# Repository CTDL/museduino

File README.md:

# museduino
an open source electronics environment for exhibits

Docs: <a href="https://museduino.org">museduino.org</a>

## PCB design files and Schematics

All files are under <a href="https://github.com/CTDL/museduino/tree/master/hardware">hardware</a>  folder and subdivided by PCB design software.

ExpressPCB folder contains versions 2.2 and below. Kicad folder is organized by board name contains its own versions (3.0 or greater).

View changelog.md for further information on changes between versions.

## Tutorials and Circuit Diagrams
Content for workshops and Museduino guides can be found under 
<a href="https://github.com/CTDL/museduino/tree/master/tutorials">tutorials</a> folder.

## Solder Instructions
Component guides and step-by-step instructions coming soon.
<a href="https://github.com/CTDL/museduino/tree/master/solder-instructions">solder-instructions</a> folder.

## Open Source
Museduino 4.0 is certified as OSHWA-compliant open source hardware.

<a href="https://certification.oshwa.org/us002128.html">certification.oshwa.org/us002128.html</a>

## License

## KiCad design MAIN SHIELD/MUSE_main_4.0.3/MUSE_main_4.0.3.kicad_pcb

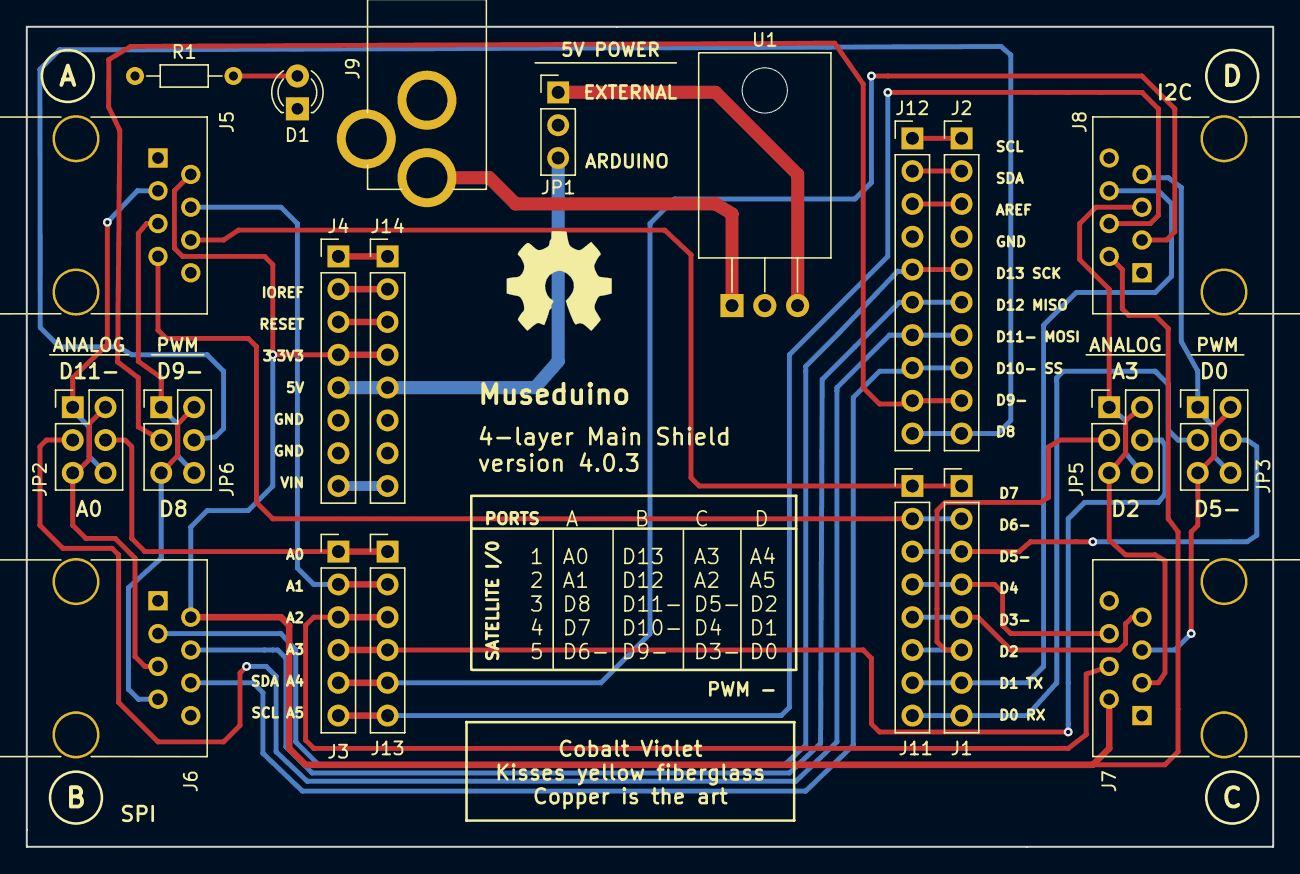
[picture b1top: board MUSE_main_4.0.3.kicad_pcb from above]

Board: 4 copper layers, 96.5 x 63.5 mm, 21 parts (0 on the bottom side), 42 nets.

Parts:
D1: LED; LED_D3.0mm
J1, J4, J11, J14: CONN_01X08; Pin_Header_Straight_1x08_Pitch2.54mm
J2, J12: CONN_01X10; Pin_Header_Straight_1x10_Pitch2.54mm
J3, J13: CONN_01X06; Pin_Header_Straight_1x06_Pitch2.54mm
J5, J6, J7, J8: CONN_01X08; RJ45_8
J9: BARREL_JACK; BARREL_JACK_RND
JP1: CONN_01X03; Pin_Header_Straight_1x03_Pitch2.54mm
JP2, JP3, JP5, JP6: CONN_02X03; Pin_Header_Straight_2x03_Pitch2.54mm
R1: 470; R_Axial_DIN0204_L3.6mm_D1.6mm_P7.62mm_Horizontal
U1: LM7805CT; TO-220_Horizontal

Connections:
+3V3: J4.4, J5.2, J6.2, J7.2, J8.2, J14.4
+5V: J5.1, J6.1, J7.1, J8.1, JP1.2, R1.1
+5V-ARD: J4.5, J14.5, JP1.3
+5V_REG: JP1.1, U1.3
A0: J3.1, J13.1, JP2.4
A1: J3.2, J5.4, J13.2
A2: J3.3, J7.4, J13.3
A3: J3.4, J13.4, JP5.4
A4_SDA: J3.5, J8.3, J13.5
A5_SCL: J3.6, J8.4, J13.6
AREF: J2.3, J12.3
D0: J1.8, J11.8, JP3.3
D1: J1.7, J8.6, J11.7
D2: J1.6, J11.6, JP5.3
D3: J1.5, J7.7, J11.5
D4: J1.4, J7.6, J11.4
D5: J1.3, J11.3, JP3.4
D6: J1.2, J5.7, J11.2
D7: J1.1, J5.6, J11.1
D8: J2.10, J12.10, JP6.4
D9: J2.9, J12.9, JP6.3
D10: J2.8, J6.6, J12.8
D11: J2.7, J12.7, JP2.3
D12: J2.6, J6.4, J12.6
D13: J2.5, J6.3, J12.5
GND: D1.1, J2.4, J4.6, J4.7, J5.8, J6.8, J7.8, J8.8, J9.2, J12.4, J14.6, J14.7, U1.2
IO-REF: J4.2, J14.2
J2-1: J2.1, J12.1
J2-2: J2.2, J12.2
J4-1: J4.1, J14.1
J5-3: J5.3, JP2.1, JP2.6
J5-5: J5.5, JP6.1, JP6.6
J6-5: J6.5, JP2.2, JP2.5
J6-7: J6.7, JP6.2, JP6.5
J7-3: J7.3, JP5.2, JP5.5
J7-5: J7.5, JP3.2, JP3.5
J8-5: J8.5, JP5.1, JP5.6
J8-7: J8.7, JP3.1, JP3.6
unnamed: D1.2, R1.2
unnamed: J9.1, U1.1
RST: J4.3, J14.3
Vin: J4.8, J14.8

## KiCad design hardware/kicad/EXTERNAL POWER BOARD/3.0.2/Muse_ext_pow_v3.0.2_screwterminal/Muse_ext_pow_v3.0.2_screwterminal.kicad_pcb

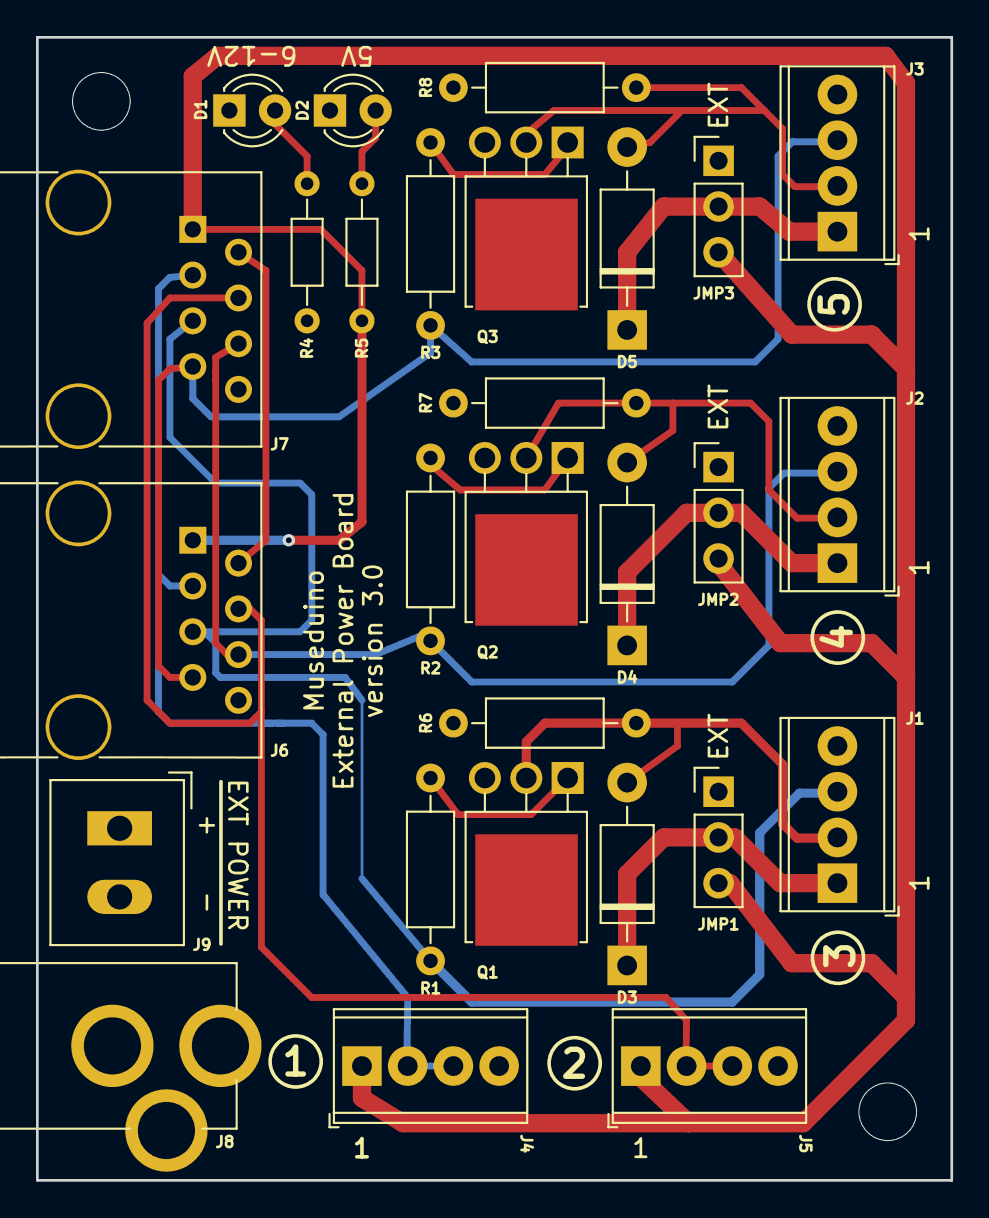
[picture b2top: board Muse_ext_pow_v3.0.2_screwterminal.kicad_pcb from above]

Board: 4 copper layers, 50.8 x 63.5 mm, 30 parts (0 on the bottom side), 20 nets.

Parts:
D1, D2: LED; LED_D3.0mm
D3, D4, D5: 1N4001; D_DO-41_SOD81_P10.16mm_Horizontal
J1, J2, J3, J4, J5: CONN_01X04; TerminalBlock_Phoenix_MPT-0,5-4-2.54_1x04_P2.54mm_Horizontal
J6, J7: RJ45_01X08; RJ45_8
J8: Barrel_Jack; BARREL_JACK_RND
J9: Conn_01x02; FCI_3.81-mm_screw_terminal
JMP1, JMP2, JMP3: Conn_01x03_Male; Pin_Header_Straight_1x03_Pitch2.54mm
Mount_Hole: MountingHole_3.2mm_M3
Mount_hole: MountingHole_3.2mm_M3
Q1, Q2, Q3: NTD3055L104-1G; TO-251-1EP_IPAK_Horizontal_smorg
R1, R2, R3: 220; R_Axial_DIN0207_L6.3mm_D2.5mm_P10.16mm_Horizontal
R4, R5: 470; R_Axial_DIN0204_L3.6mm_D1.6mm_P7.62mm_Horizontal
R6, R7, R8: 10k; R_Axial_DIN0207_L6.3mm_D2.5mm_P10.16mm_Horizontal

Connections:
+3V3: J6.2, J7.2
+5V: J4.1, J5.1, J6.1, J7.1, JMP1.3, JMP2.3, JMP3.3, R5.1
GND: D1.1, D2.1, J1.4, J2.4, J3.4, J4.4, J5.4, J6.8, J7.8, J8.2, J9.2, Q1.3, Q2.3, Q3.3, R6.2, R7.2, R8.2
unnamed: D1.2, R4.2
unnamed: D2.2, R5.2
unnamed: D3.2, J1.2, Q1.2, R6.1
unnamed: D4.2, J2.2, Q2.2, R7.1
unnamed: D5.2, J3.2, Q3.2, R8.1
unnamed: Q1.1, R1.1
unnamed: Q2.1, R2.1
unnamed: Q3.1, R3.1
Sense_1: J4.2, J4.3, J6.3, J7.3
Sense_2: J5.2, J5.3, J6.4, J7.4
Sense_3: J1.3, J6.5, J7.5, R1.2
Sense_4: J2.3, J6.6, J7.6, R2.2
Sense_5: J3.3, J6.7, J7.7, R3.2
Ve3: D3.1, J1.1, JMP1.2
Ve4: D4.1, J2.1, JMP2.2
Ve5: D5.1, J3.1, JMP3.2
Vext: J8.1, J9.1, JMP1.1, JMP2.1, JMP3.1, R4.1

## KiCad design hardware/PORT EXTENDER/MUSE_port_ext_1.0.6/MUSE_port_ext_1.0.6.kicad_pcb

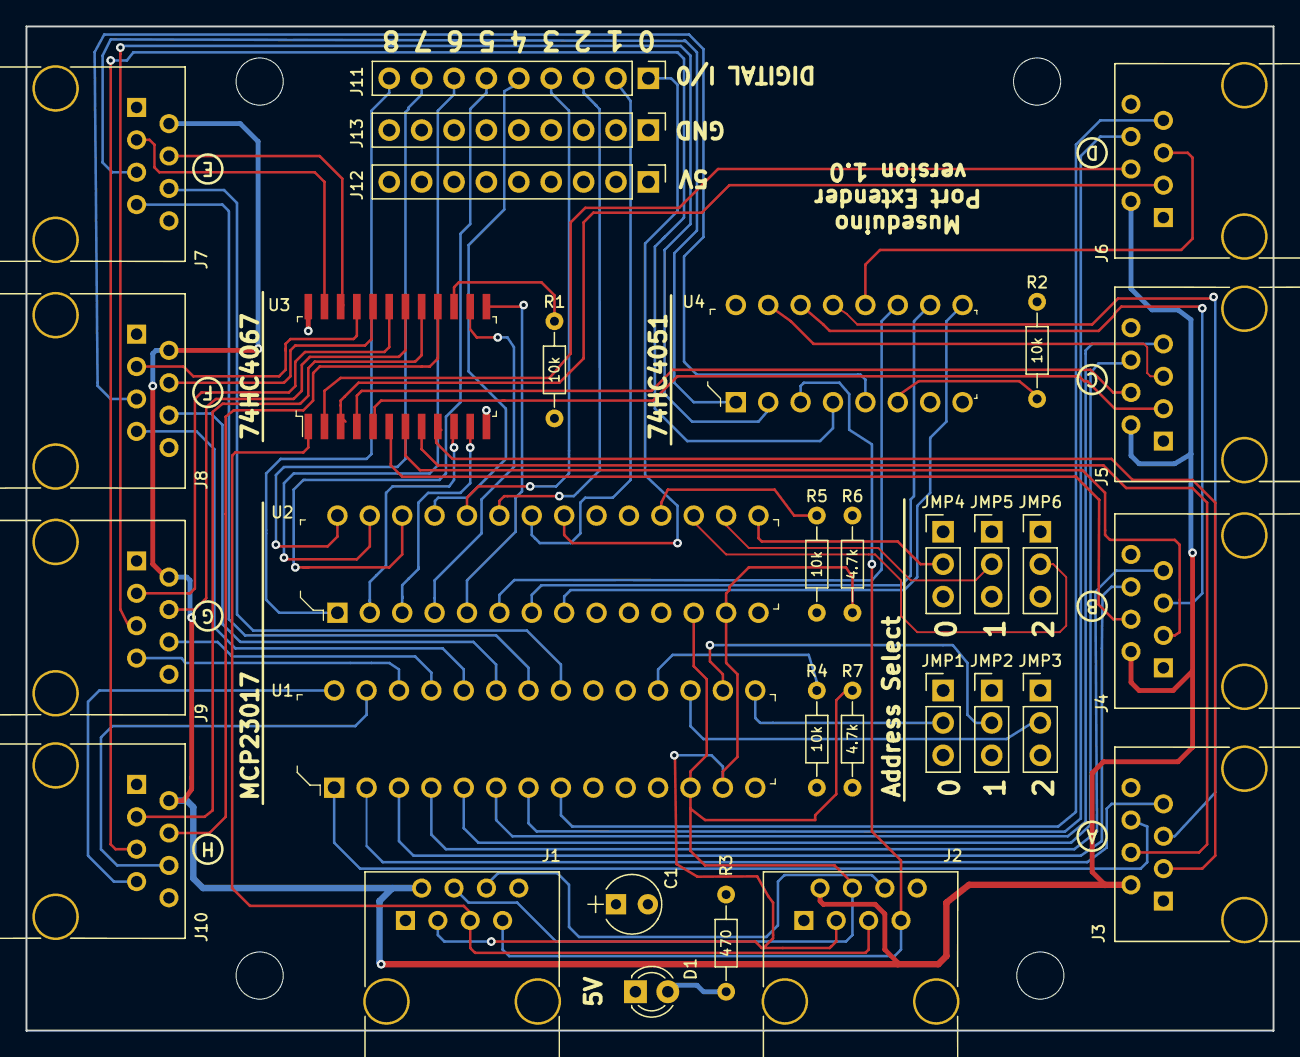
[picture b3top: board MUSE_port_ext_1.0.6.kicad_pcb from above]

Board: 4 copper layers, 97.8 x 78.7 mm, 32 parts (0 on the bottom side), 75 nets.

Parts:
C1: 0.1; CP_Radial_Tantal_D4.5mm_P2.50mm
D1: LED; LED_D3.0mm
J1, J2, J3, J4, J5, J6, J7, J8, J9, J10: RJ45_01X08; RJ45_8
J11, J12, J13: Conn_01x09; Pin_Header_Straight_1x09_Pitch2.54mm
JMP1, JMP2, JMP3, JMP4, JMP5, JMP6: Conn_01x03; Pin_Header_Straight_1x03_Pitch2.54mm
R1, R2, R4, R5: 10K; R_Axial_DIN0204_L3.6mm_D1.6mm_P7.62mm_Horizontal
R3: 470; R_Axial_DIN0204_L3.6mm_D1.6mm_P7.62mm_Horizontal
R6, R7: 4.7K; R_Axial_DIN0204_L3.6mm_D1.6mm_P7.62mm_Horizontal
U1, U2: MCP23017-E_SP; DIP-28_W7.62mm
U3: CD74HC4067SM96; SSOP-24_W5.30mm
U4: CD74HC4051E; DIP-16_W7.62mm

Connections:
+3V3: J1.2, J2.2, J3.2, J4.2, J5.2, J6.2, J7.2, J8.2, J9.2, J10.2
+5V: C1.1, J1.1, J2.1, J3.1, J4.1, J5.1, J6.1, J7.1, J8.1, J9.1, J10.1, J12.1, J12.2, J12.3, J12.4, J12.5, J12.6, J12.7, J12.8, J12.9, JMP1.1, JMP2.1, JMP3.1, JMP4.1, JMP5.1, JMP6.1, R3.1, R4.1, R5.1, R6.1, R7.1, U1.9, U2.9, U3.24, U4.16
A1_OUT1: J3.3, U3.9
A1_OUT2: J4.3, U3.7
A1_OUT3: J5.3, U3.5
A1_OUT4: J6.3, U3.3
A1_OUT5: J7.3, U3.23
A1_OUT6: J8.3, U3.21
A1_OUT7: J9.3, U3.19
A1_OUT8: J10.3, U3.17
A2_OUT1: J3.4, U3.8
A2_OUT2: J4.4, U3.6
A2_OUT3: J5.4, U3.4
A2_OUT4: J6.4, U3.2
A2_OUT5: J7.4, U3.22
A2_OUT6: J8.4, U3.20
A2_OUT7: J9.4, U3.18
A2_OUT8: J10.4, U3.16
AMUX_8_S0: U2.6, U4.11
AMUX_8_S1: U2.7, U4.10
AMUX_8_S2: U2.8, U4.9
AMUX_16_COM_IN: J1.5, J2.5, U3.1
AMUX_16_S0: U2.2, U3.10
AMUX_16_S1: U2.3, U3.11
AMUX_16_S2: U2.4, U3.14
AMUX_16_S3: U2.5, U3.13
D1_OUT1: J3.6, U1.1
D1_OUT2: J4.6, U1.3
D1_OUT3: J5.6, U1.5
D1_OUT4: J6.6, U1.7
D1_OUT5: J7.6, U1.21
D1_OUT6: J8.6, U1.23
D1_OUT7: J9.6, U1.25
D1_OUT8: J10.6, U1.27
D2_INP: J1.6, J2.6
D2_OUT1: J3.7, U1.2
D2_OUT2: J4.7, U1.4
D2_OUT3: J5.7, U1.6
D2_OUT4: J6.7, U1.8
D2_OUT5: J7.7, U1.22
D2_OUT6: J8.7, U1.24
D2_OUT7: J9.7, U1.26
D2_OUT8: J10.7, U1.28
GND: C1.2, D1.1, J1.8, J2.8, J3.8, J4.8, J5.8, J6.8, J7.8, J8.8, J9.8, J10.8, J13.1, J13.2, J13.3, J13.4, J13.5, J13.6, J13.7, J13.8, J13.9, JMP1.3, JMP2.3, JMP3.3, JMP4.3, JMP5.3, JMP6.3, R1.2, R2.2, U1.10, U2.10, U3.12, U4.7
HDR_D1: J11.1, U2.21
HDR_D2: J11.2, U2.22
HDR_D3: J11.3, U2.23
HDR_D4: J11.4, U2.24
HDR_D5: J11.5, U2.25
HDR_D6: J11.6, U2.26
HDR_D7: J11.7, U2.27
HDR_D8: J11.8, U2.28
HDR_D9: J11.9, U2.1
unnamed: D1.2, R3.2
unnamed: R1.1, U3.15
unnamed: R2.1, U4.6
unnamed: R4.2, U1.18
unnamed: R5.2, U2.18
PWM_COM_OUT: J1.7, J2.7, U4.3
PWM_OUT1: J3.5, U4.13
PWM_OUT2: J4.5, U4.14
PWM_OUT3: J5.5, U4.15
PWM_OUT4: J6.5, U4.12
PWM_OUT5: J7.5, U4.1
PWM_OUT6: J8.5, U4.5
PWM_OUT7: J9.5, U4.2
PWM_OUT8: J10.5, U4.4
SCL: J1.4, J2.4, R7.2, U1.12, U2.12
SDA: J1.3, J2.3, R6.2, U1.13, U2.13
U1_A0: JMP1.2, U1.15
U1_A1: JMP2.2, U1.16
U1_A2: JMP3.2, U1.17
U2_A0: JMP4.2, U2.15
U2_A1: JMP5.2, U2.16
U2_A2: JMP6.2, U2.17

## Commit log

2015-06-08 Create Button
2015-06-08 Rename Button to Button.ino
2015-08-11 Create PWMServo
2015-08-11 Create DCMotor
2015-08-11 Rename PWMServo to PWMServo.ino
2015-08-11 Rename DCMotor to DCMotor.ino
2016-10-04 PCB Schematic
2020-01-06 tutorial updates
2020-01-06 ciruit diagrams pdf
2020-01-06 grouped folders
2020-01-06 additional code samples
2020-01-06 pcb design files and schematics
2022-06-22 reorganize
2022-07-15 update archive
2022-07-15 tutorials
2022-07-20 express pcb versions
2022-10-04 licensing
2022-10-06 certification
2022-10-06 logo
2022-10-06 svgs
2022-10-06 pathfix
